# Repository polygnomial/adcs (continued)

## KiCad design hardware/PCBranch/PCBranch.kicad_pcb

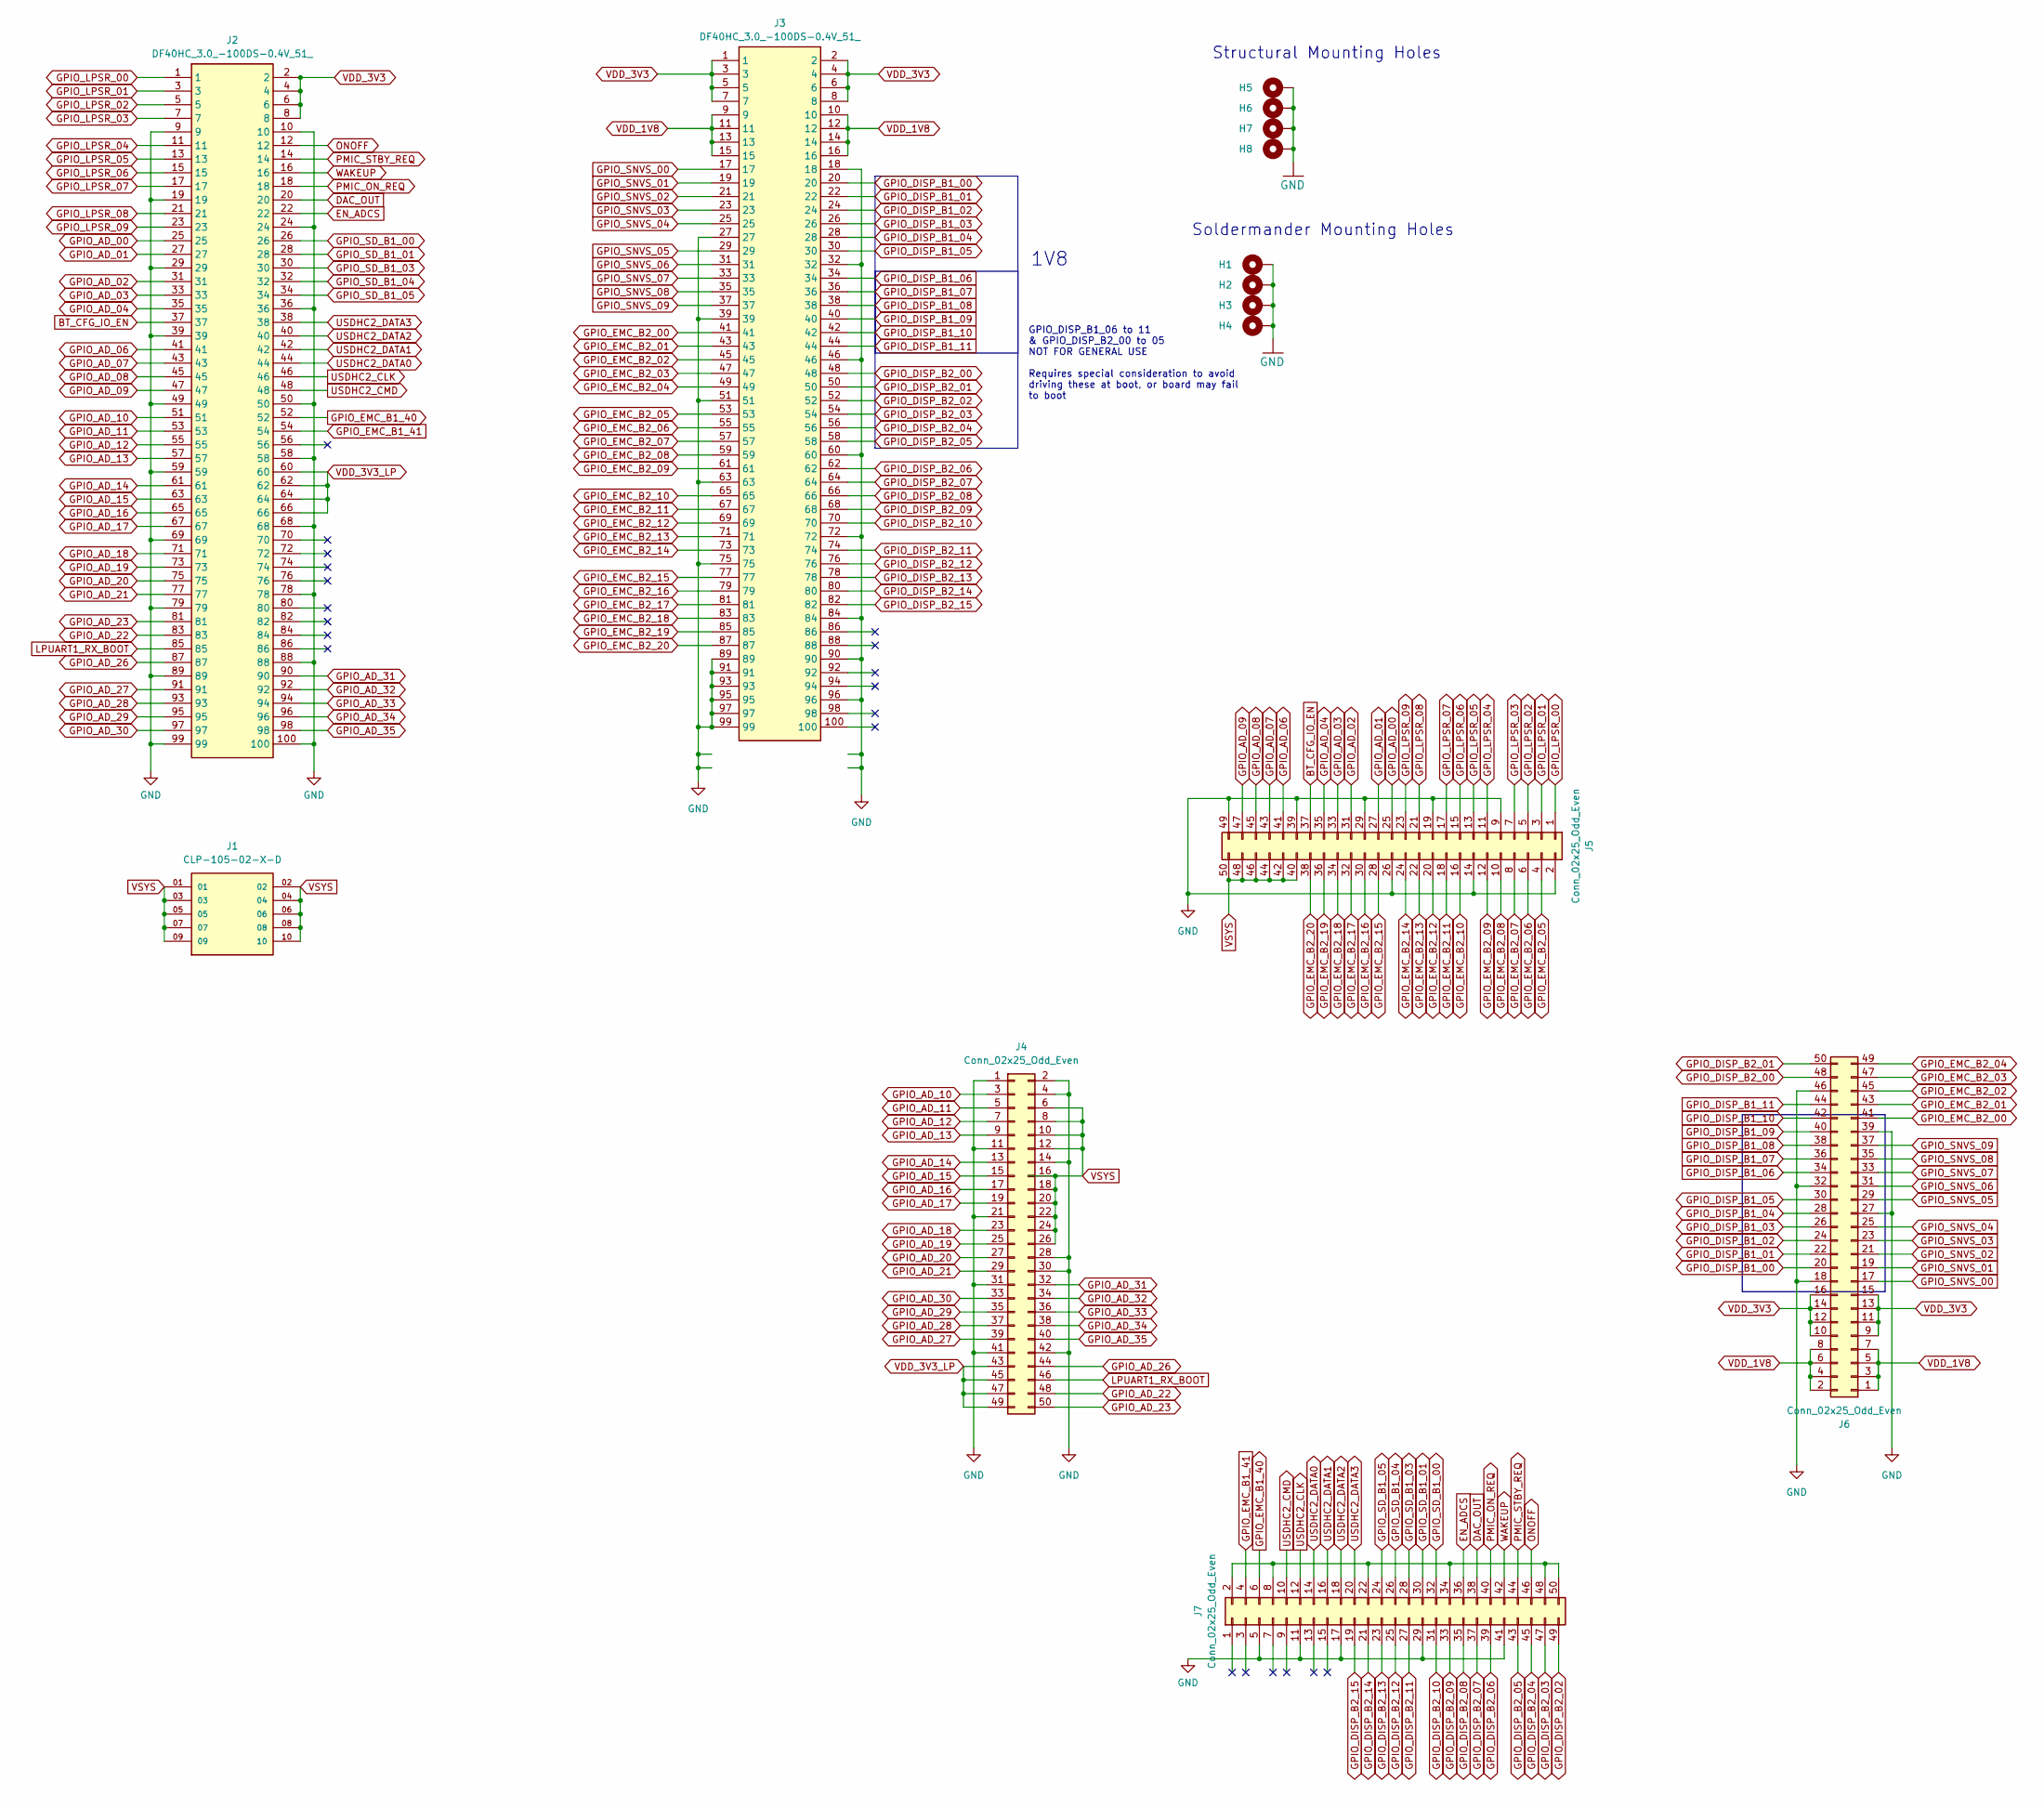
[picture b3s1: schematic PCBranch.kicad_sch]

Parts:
H1, H2, H3, H4: MountingHole_Pad; MountingHole_2.7mm_M2.5_DIN965_Pad
H5, H6, H7, H8: MountingHole_Pad; MountingHole_3.2mm_M3_DIN965_Pad
J1: CLP-105-02-X-D; SAMTEC_CLP-105-02-X-D; PARTREV V
J2, J3: DF40HC_3.0_-100DS-0.4V_51_; DF40HC30100DS04V51; Manufacturer_Part_Number DF40HC(3.0)-100DS-0.4V(51)
J4, J5, J6, J7: Conn_02x25_Odd_Even; PinHeader_2x25_P2.54mm_Vertical

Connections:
BT_CFG_IO_EN: J2.37, J5.37
DAC_OUT: J2.20, J7.38
EN_ADCS: J2.22, J7.36
GND: H1.1, H2.1, H3.1, H4.1, H5.1, H6.1, H7.1, H8.1, J2.9, J2.10, J2.19, J2.24, J2.29, J2.36, J2.39, J2.49, J2.50, J2.58, J2.59, J2.68, J2.69, J2.78, J2.79, J2.88, J2.89, J2.99, J2.100, J3.18, J3.27, J3.32, J3.39, J3.46, J3.51, J3.60, J3.63, J3.72, J3.75, J3.84, J3.89, J3.90, J3.91, J3.93, J3.95, J3.96, J3.97, J3.99, J4.1, J4.2, J4.4, J4.11, J4.14, J4.21, J4.28, J4.30, J4.31, J4.41, J4.42, J5.2, J5.9, J5.14, J5.19, J5.26, J5.29, J5.39, J5.49, J6.18, J6.27, J6.32, J6.39, J6.46, J7.5, J7.11, J7.17, J7.29, J7.41
GPIO_AD_00: J2.25, J5.25
GPIO_AD_01: J2.27, J5.27
GPIO_AD_02: J2.31, J5.31
GPIO_AD_03: J2.33, J5.33
GPIO_AD_04: J2.35, J5.35
GPIO_AD_06: J2.41, J5.41
GPIO_AD_07: J2.43, J5.43
GPIO_AD_08: J2.45, J5.45
GPIO_AD_09: J2.47, J5.47
GPIO_AD_10: J2.51, J4.3
GPIO_AD_11: J2.53, J4.5
GPIO_AD_12: J2.55, J4.7
GPIO_AD_13: J2.57, J4.9
GPIO_AD_14: J2.61, J4.13
GPIO_AD_15: J2.63, J4.15
GPIO_AD_16: J2.65, J4.17
GPIO_AD_17: J2.67, J4.19
GPIO_AD_18: J2.71, J4.23
GPIO_AD_19: J2.73, J4.25
GPIO_AD_20: J2.75, J4.27
GPIO_AD_21: J2.77, J4.29
GPIO_AD_22: J2.83, J4.48
GPIO_AD_23: J2.81, J4.50
GPIO_AD_26: J2.87, J4.44
GPIO_AD_27: J2.91, J4.39
GPIO_AD_28: J2.93, J4.37
GPIO_AD_29: J2.95, J4.35
GPIO_AD_30: J2.97, J4.33
GPIO_AD_31: J2.90, J4.32
GPIO_AD_32: J2.92, J4.34
GPIO_AD_33: J2.94, J4.36
GPIO_AD_34: J2.96, J4.38
GPIO_AD_35: J2.98, J4.40
GPIO_DISP_B1_00: J3.20, J6.20
GPIO_DISP_B1_01: J3.22, J6.22
GPIO_DISP_B1_02: J3.24, J6.24
GPIO_DISP_B1_03: J3.26, J6.26
GPIO_DISP_B1_04: J3.28, J6.28
GPIO_DISP_B1_05: J3.30, J6.30
GPIO_DISP_B1_06: J3.34, J6.34
GPIO_DISP_B1_07: J3.36, J6.36
GPIO_DISP_B1_08: J3.38, J6.38
GPIO_DISP_B1_09: J3.40, J6.40
GPIO_DISP_B1_10: J3.42, J6.42
GPIO_DISP_B1_11: J3.44, J6.44
GPIO_DISP_B2_00: J3.48, J6.48
GPIO_DISP_B2_01: J3.50, J6.50
GPIO_DISP_B2_02: J3.52, J7.49
GPIO_DISP_B2_03: J3.54, J7.47
GPIO_DISP_B2_04: J3.56, J7.45
GPIO_DISP_B2_05: J3.58, J7.43
GPIO_DISP_B2_06: J3.62, J7.39
GPIO_DISP_B2_07: J3.64, J7.37
GPIO_DISP_B2_08: J3.66, J7.35
GPIO_DISP_B2_09: J3.68, J7.33
GPIO_DISP_B2_10: J3.70, J7.31
GPIO_DISP_B2_11: J3.74, J7.27
GPIO_DISP_B2_12: J3.76, J7.25
GPIO_DISP_B2_13: J3.78, J7.23
GPIO_DISP_B2_14: J3.80, J7.21
GPIO_DISP_B2_15: J3.82, J7.19
GPIO_EMC_B1_40: J2.52, J7.6
GPIO_EMC_B1_41: J2.54, J7.4
GPIO_EMC_B2_00: J3.41, J6.41
GPIO_EMC_B2_01: J3.43, J6.43
GPIO_EMC_B2_02: J3.45, J6.45
GPIO_EMC_B2_03: J3.47, J6.47
GPIO_EMC_B2_04: J3.49, J6.49
GPIO_EMC_B2_05: J3.53, J5.4
GPIO_EMC_B2_06: J3.55, J5.6
GPIO_EMC_B2_07: J3.57, J5.8
GPIO_EMC_B2_08: J3.59, J5.10
GPIO_EMC_B2_09: J3.61, J5.12
GPIO_EMC_B2_10: J3.65, J5.16
GPIO_EMC_B2_11: J3.67, J5.18
GPIO_EMC_B2_12: J3.69, J5.20
GPIO_EMC_B2_13: J3.71, J5.22
GPIO_EMC_B2_14: J3.73, J5.24
GPIO_EMC_B2_15: J3.77, J5.28
GPIO_EMC_B2_16: J3.79, J5.30
GPIO_EMC_B2_17: J3.81, J5.32
GPIO_EMC_B2_18: J3.83, J5.34
GPIO_EMC_B2_19: J3.85, J5.36
GPIO_EMC_B2_20: J3.87, J5.38
GPIO_LPSR_00: J2.1, J5.1
GPIO_LPSR_01: J2.3, J5.3
GPIO_LPSR_02: J2.5, J5.5
GPIO_LPSR_03: J2.7, J5.7
GPIO_LPSR_04: J2.11, J5.11
GPIO_LPSR_05: J2.13, J5.13
GPIO_LPSR_06: J2.15, J5.15
GPIO_LPSR_07: J2.17, J5.17
GPIO_LPSR_08: J2.21, J5.21
GPIO_LPSR_09: J2.23, J5.23
GPIO_SD_B1_00: J2.26, J7.32
GPIO_SD_B1_01: J2.28, J7.30
GPIO_SD_B1_03: J2.30, J7.28
GPIO_SD_B1_04: J2.32, J7.26
GPIO_SD_B1_05: J2.34, J7.24
GPIO_SNVS_00: J3.17, J6.17
GPIO_SNVS_01: J3.19, J6.19
GPIO_SNVS_02: J3.21, J6.21
GPIO_SNVS_03: J3.23, J6.23
GPIO_SNVS_04: J3.25, J6.25
GPIO_SNVS_05: J3.29, J6.29
GPIO_SNVS_06: J3.31, J6.31
GPIO_SNVS_07: J3.33, J6.33
GPIO_SNVS_08: J3.35, J6.35
GPIO_SNVS_09: J3.37, J6.37
LPUART1_RX_BOOT: J2.85, J4.46
unnamed: J7.2, J7.8, J7.22, J7.34, J7.48, J7.50
ONOFF: J2.12, J7.46
PMIC_ON_REQ: J2.18, J7.40
PMIC_STBY_REQ: J2.14, J7.44
USDHC2_CLK: J2.46, J7.12
USDHC2_CMD: J2.48, J7.10
USDHC2_DATA0: J2.44, J7.14
USDHC2_DATA1: J2.42, J7.16
USDHC2_DATA2: J2.40, J7.18
USDHC2_DATA3: J2.38, J7.20
VDD_1V8: J3.9, J3.10, J3.11, J3.12, J3.13, J3.14, J3.15, J3.16, J6.1, J6.2, J6.3, J6.4, J6.5, J6.6, J6.7, J6.8
VDD_3V3: J2.2, J2.4, J2.6, J2.8, J3.1, J3.2, J3.3, J3.4, J3.5, J3.6, J3.7, J3.8, J6.9, J6.10, J6.11, J6.12, J6.13, J6.14, J6.15, J6.16
VDD_3V3_LP: J2.60, J2.62, J2.64, J2.66, J4.43, J4.45, J4.47, J4.49
VSYS: J1.01, J1.02, J1.03, J1.04, J1.05, J1.06, J1.07, J1.08, J1.09, J1.10, J4.6, J4.8, J4.10, J4.12, J4.16, J4.18, J4.20, J4.22, J4.24, J4.26, J5.40, J5.42, J5.44, J5.46, J5.48, J5.50
WAKEUP: J2.16, J7.42

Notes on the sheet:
1V8
Soldermander Mounting Holes
Structural Mounting Holes
GPIO_DISP_B1_06 to 11 & GPIO_DISP_B2_00 to 05 NOT FOR GENERAL USE Requires special consideration to avoid driving these at boot, or board may fail to boot

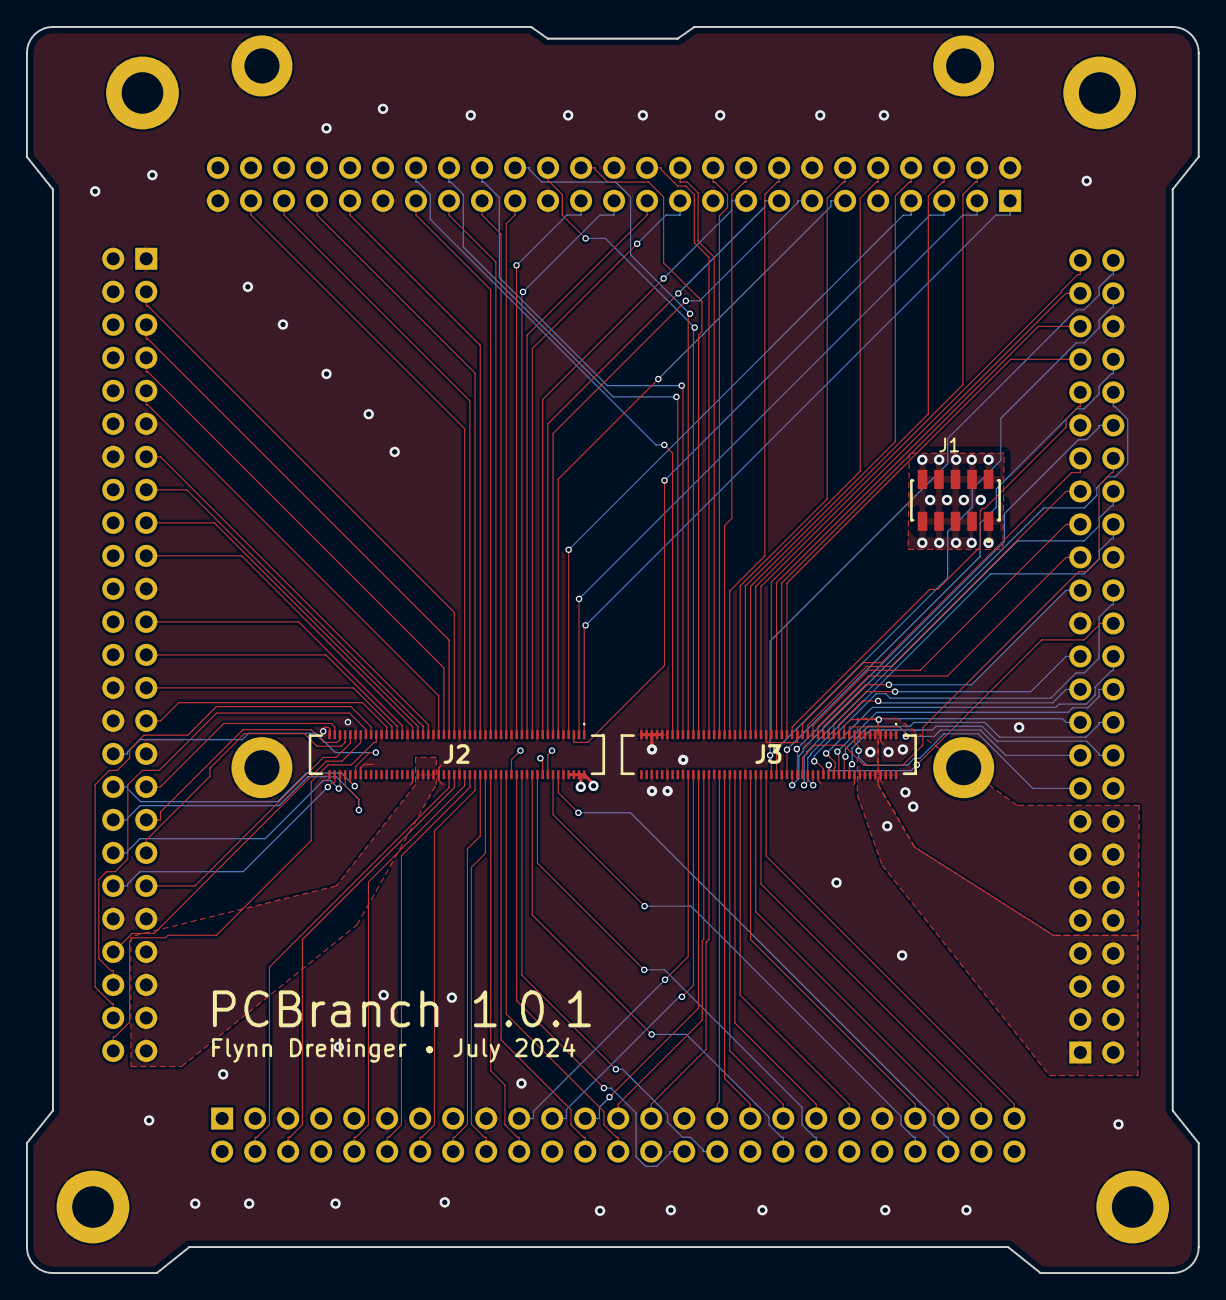
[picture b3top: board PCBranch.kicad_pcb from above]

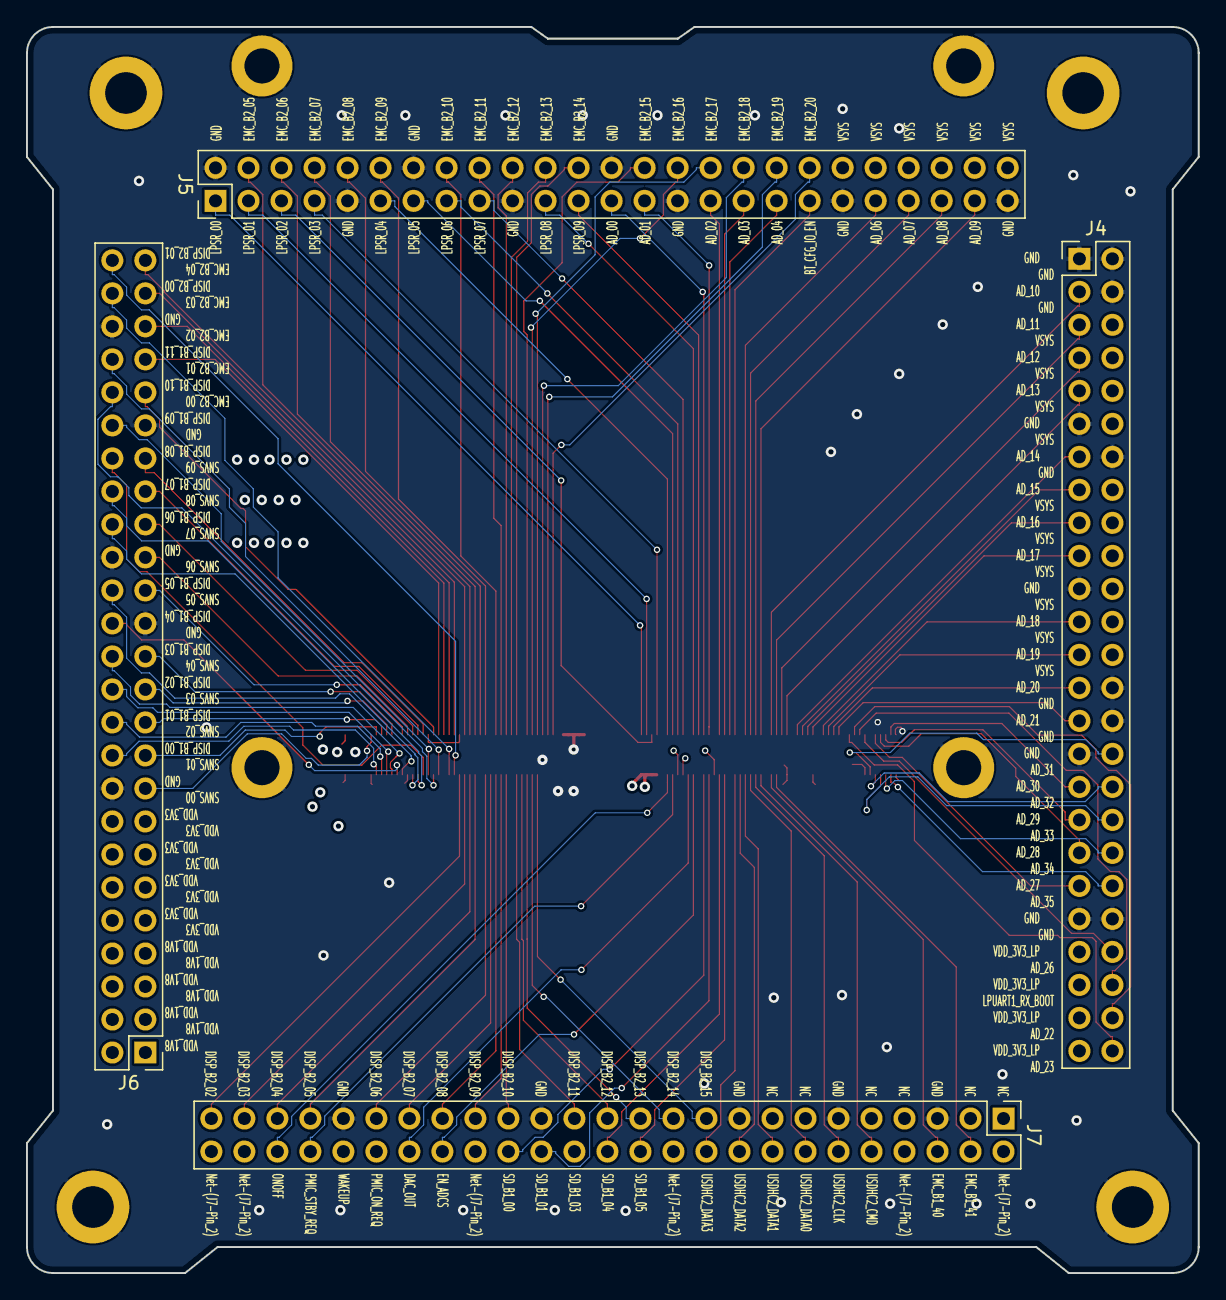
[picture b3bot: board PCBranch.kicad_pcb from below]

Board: 4 copper layers, 90.2 x 95.9 mm, 15 parts (4 on the bottom side), 129 nets.

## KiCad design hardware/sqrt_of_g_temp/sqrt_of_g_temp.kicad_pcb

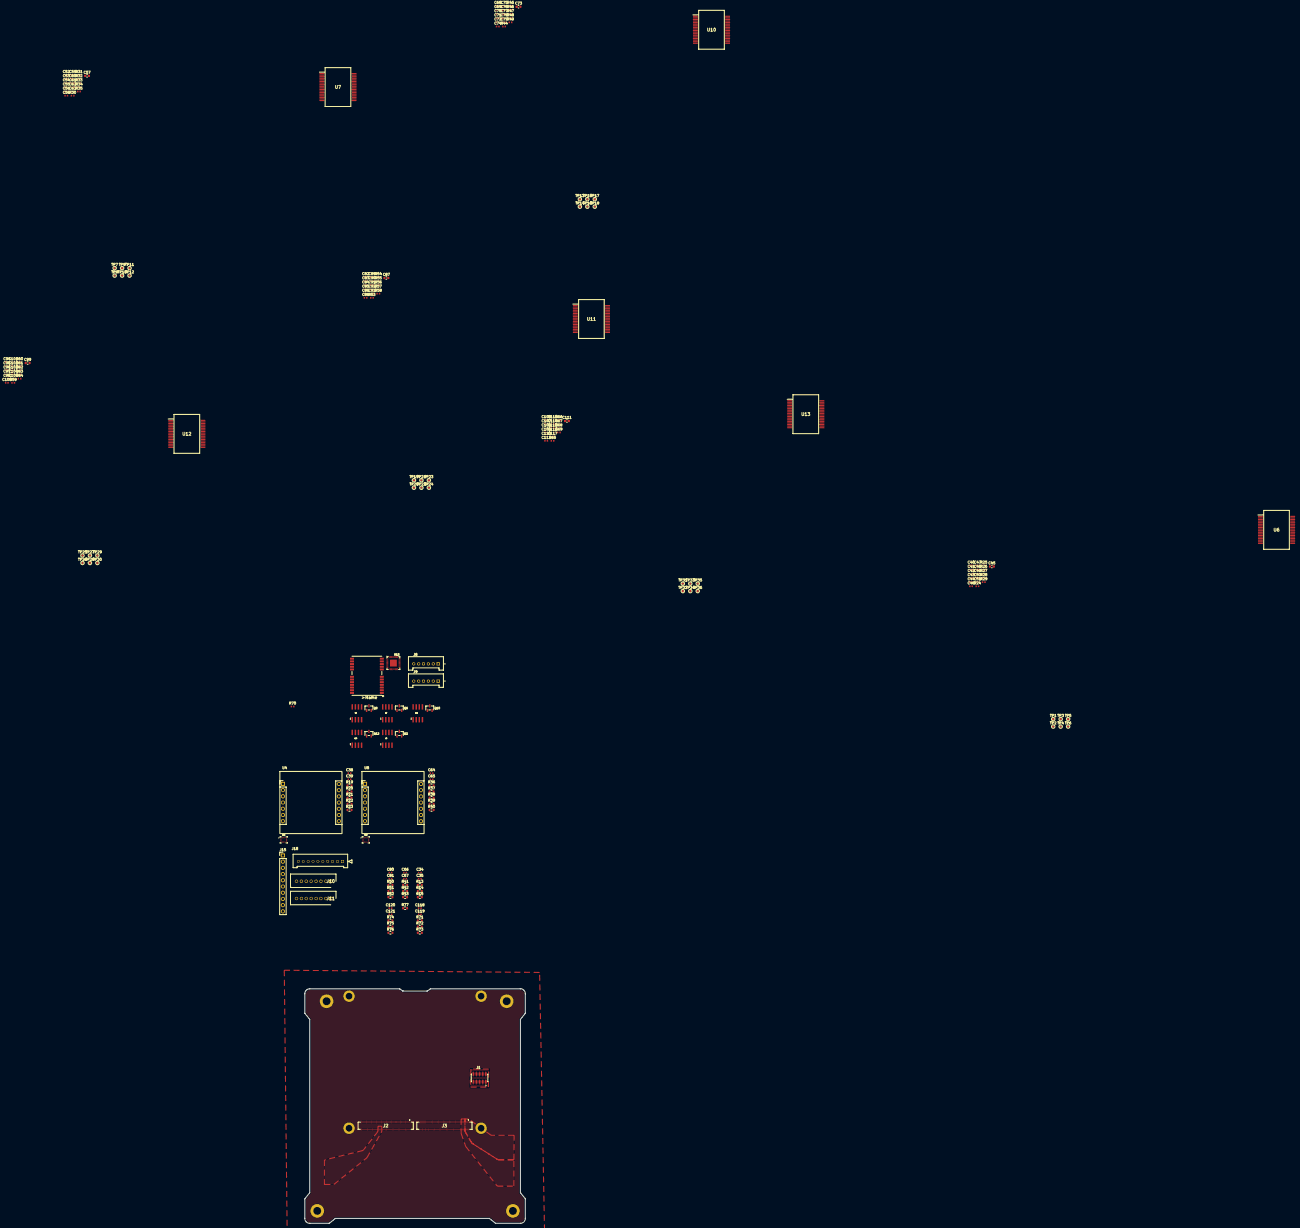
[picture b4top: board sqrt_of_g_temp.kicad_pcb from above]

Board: 4 copper layers, 90.2 x 95.9 mm, 223 parts (0 on the bottom side), 128 nets, no tracks yet.

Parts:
C34, C66, C80, C118, C120: 10nF; Perfect_0402
C35, C67, C81, C119, C121: 4.7uF; Perfect_0402
C38, C39, C48, C50, C51, C60, C62, C63, C64, C65, C76, C78, C79, C90, C92, C93, C102, C104, C105, C114, C116, C117: 0.1uF; Perfect_0402
C40, C41, C42, C44, C46, C47, C49, C52, C53, C54, C56, C58, C59, C61, C68, C69, C70, C72, C74, C75, C77, C82, C83, C84, C86, C88, C89, C91, C94, C95, C96, C98, C100, C101, C103, C106, C107, C108, C110, C112, C113, C115: 100nF; Perfect_0402
C43, C55, C71, C85, C97, C109: 1uF; Perfect_0402
C45, C57, C73, C87, C99, C111: 47uF; C_0603_1608Metric
H1, H2, H3, H4: MountingHole_Pad; MountingHole_2.7mm_M2.5_DIN965_Pad
H5, H6, H7, H8: MountingHole_Pad; MountingHole_3.2mm_M3_DIN965_Pad
J1: CLP-105-02-X-D; SAMTEC_CLP-105-02-X-D
J2, J3: DF40HC_3.0_-100DS-0.4V_51_; DF40HC30100DS04V51
J8, J9: 353620650; MOLEX_35362-0650
J10, J11: 353620850; SHDR8W50P0X200_1X8_1830X550X850P
J15: Conn_01x10; PinHeader_1x10_P2.54mm_Vertical
J18: Thruster Connector; CON_353621050
Q2, Q6, Q8, Q10, Q12: IRLML2803; SOT-23
Q3, Q7, Q9, Q11, Q13: NDS8434
R13, R41, R50, R71, R74, R77: 10K; R_0603_1608Metric
R14, R42, R51, R72, R75: 4.7K; R_0603_1608Metric
R15, R43, R52, R73, R76: 3.3k; R_0603_1608Metric
R19, R20, R21, R22, R23, R36, R37, R38, R39, R40: 10k; R_0603_1608Metric
R24, R27, R28, R29, R30, R33, R34, R35, R44, R47, R48, R49, R53, R56, R57, R58, R59, R62, R63, R64, R65, R68, R69, R70: 10k; Perfect_0402
R25, R31, R45, R54, R60, R66: 36k; Perfect_0402
R26, R32, R46, R55, R61, R67: 1; Perfect_0402
TP1, TP2, TP3, TP4, TP5, TP6, TP7, TP8, TP9, TP10, TP11, TP12, TP13, TP14, TP15, TP16, TP17, TP18, TP19, TP20, TP21, TP22, TP23, TP24, TP25, TP26, TP27, TP28, TP29, TP30, TP31, TP32, TP33, TP34, TP35, TP36: TestPoint; TestPoint_Pad_D1.0mm
U4, U8: RM3100 Dev Board; RM3100
U5, U9: BMI270; XDCR_BMI270
U6, U7, U10, U11, U12, U13: DRV8332DKDR; SOP65P1420X360-36N
U14: Orion B16; S1216_24PIN_PACKAGE
U15: EP2W+; QFN32-5X5MM

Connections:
+3V3: J15.1, Q3.1 (Source), Q3.2 (Source), Q3.3 (Source), Q7.1 (Source), Q7.2 (Source), Q7.3 (Source), Q9.1 (Source), Q9.2 (Source), Q9.3 (Source), Q11.1 (Source), Q11.2 (Source), Q11.3 (Source), Q13.1 (Source), Q13.2 (Source), Q13.3 (Source), R15.1, R43.1, R52.1, R73.1, R76.1
+12V: C43.2, C45.2, C46.1, C47.1, C48.1, C49.1, C50.1, C51.1, C55.2, C57.2, C58.1, C59.1, C60.1, C61.1, C62.1, C63.1, C71.2, C73.2, C74.1, C75.1, C76.1, C77.1, C78.1, C79.1, C85.2, C87.2, C88.1, C89.1, C90.1, C91.1, C92.1, C93.1, C97.2, C99.2, C100.1, C101.1, C102.1, C103.1, C104.1, C105.1, C109.2, C111.2, C112.1, C113.1, C114.1, C115.1, C116.1, C117.1, U6.1 (GVDD_B), U6.18 (GVDD_C), U6.19 (GVDD_C), U6.21 (PVDD_C), U6.29 (PVDD_B), U6.34 (PVDD_A), U6.36 (GVDD_A), U7.1 (GVDD_B), U7.18 (GVDD_C), U7.19 (GVDD_C), U7.21 (PVDD_C), U7.29 (PVDD_B), U7.34 (PVDD_A), U7.36 (GVDD_A), U10.1 (GVDD_B), U10.18 (GVDD_C), U10.19 (GVDD_C), U10.21 (PVDD_C), U10.29 (PVDD_B), U10.34 (PVDD_A), U10.36 (GVDD_A), U11.1 (GVDD_B), U11.18 (GVDD_C), U11.19 (GVDD_C), U11.21 (PVDD_C), U11.29 (PVDD_B), U11.34 (PVDD_A), U11.36 (GVDD_A), U12.1 (GVDD_B), U12.18 (GVDD_C), U12.19 (GVDD_C), U12.21 (PVDD_C), U12.29 (PVDD_B), U12.34 (PVDD_A), U12.36 (GVDD_A), U13.1 (GVDD_B), U13.18 (GVDD_C), U13.19 (GVDD_C), U13.21 (PVDD_C), U13.29 (PVDD_B), U13.34 (PVDD_A), U13.36 (GVDD_A)
/3V3_PD1: C80.1, C81.1, J9.1, J11.1, J11.5, Q9.5 (Drain), Q9.6 (Drain), Q9.7 (Drain), Q9.8 (Drain)
/3V3_PD2: C66.1, C67.1, J8.1, J10.1, J10.5, Q7.5 (Drain), Q7.6 (Drain), Q7.7 (Drain), Q7.8 (Drain)
/GPS/3V3_GPS: C118.1, C119.1, Q11.5 (Drain), Q11.6 (Drain), Q11.7 (Drain), Q11.8 (Drain), R77.2, U14.22 (V_BCKP), U14.23 (VCC)
/GPS/EN_GPS: R71.1, R72.1
/GPS/RF_IN: U14.11 (RF_IN), U15.4 (SUM_PORT)
/IMU1_and_MAG1/3V3_SENSORS: C38.1, C39.1, C120.1, C121.1, Q13.5 (Drain), Q13.6 (Drain), Q13.7 (Drain), Q13.8 (Drain), R21.2, R22.1, R23.1, U4.12 (DVDD), U4.13 (AVDD), U5.5 (VDDIO), U5.8 (VDD), U5.10 (OSCB)
/IMU1_and_MAG1/EN_SENSORS: R74.1, R75.1
/IMU2_and_MAG2/3V3_SENSORS: C34.1, C35.1, C64.1, C65.1, Q3.5 (Drain), Q3.6 (Drain), Q3.7 (Drain), Q3.8 (Drain), R38.2, R39.1, R40.1, U8.12 (DVDD), U8.13 (AVDD), U9.5 (VDDIO), U9.8 (VDD), U9.10 (OSCB)
/IMU2_and_MAG2/EN_SENSORS: R13.1, R14.1
/Magnetorquer Controller 1/AGND: C106.1, R66.1, R67.2, U13.9 (AGND), U13.12 (M2)
/Magnetorquer Controller 1/M1: R65.2, U13.13 (M1)
/Magnetorquer Controller 1/OUT_A: C107.1, U13.33 (OUT_A)
/Magnetorquer Controller 1/OUT_B: C108.1, U13.30 (OUT_B)
/Magnetorquer Controller 1/OUT_C: C110.1, U13.22 (OUT_C)
/Magnetorquer Controller 2/AGND: C40.1, R25.1, R26.2, U6.9 (AGND), U6.12 (M2)
/Magnetorquer Controller 2/M1: R24.2, U6.13 (M1)
/Magnetorquer Controller 2/OUT_A: C41.1, U6.33 (OUT_A)
/Magnetorquer Controller 2/OUT_B: C42.1, U6.30 (OUT_B)
/Magnetorquer Controller 2/OUT_C: C44.1, U6.22 (OUT_C)
/Motor Controller 1/AGND: C82.1, R54.1, R55.2, U11.9 (AGND), U11.12 (M2)
/Motor Controller 1/M1: R53.2, U11.13 (M1)
/Motor Controller 1/OUT_A: C83.1, U11.33 (OUT_A)
/Motor Controller 1/OUT_B: C84.1, U11.30 (OUT_B)
/Motor Controller 1/OUT_C: C86.1, U11.22 (OUT_C)
/Motor Controller 2/AGND: C52.1, R31.1, R32.2, U7.9 (AGND), U7.12 (M2)
/Motor Controller 2/M1: R30.2, U7.13 (M1)
/Motor Controller 2/OUT_A: C53.1, U7.33 (OUT_A)
/Motor Controller 2/OUT_B: C54.1, U7.30 (OUT_B)
/Motor Controller 2/OUT_C: C56.1, U7.22 (OUT_C)
/Motor Controller 3/AGND: C94.1, R60.1, R61.2, U12.9 (AGND), U12.12 (M2)
/Motor Controller 3/M1: R59.2, U12.13 (M1)
/Motor Controller 3/OUT_A: C95.1, U12.33 (OUT_A)
/Motor Controller 3/OUT_B: C96.1, U12.30 (OUT_B)
/Motor Controller 3/OUT_C: C98.1, U12.22 (OUT_C)
/Motor Controller 4/AGND: C68.1, R45.1, R46.2, U10.9 (AGND), U10.12 (M2)
/Motor Controller 4/M1: R44.2, U10.13 (M1)
/Motor Controller 4/OUT_A: C69.1, U10.33 (OUT_A)
/Motor Controller 4/OUT_B: C70.1, U10.30 (OUT_B)
/Motor Controller 4/OUT_C: C72.1, U10.22 (OUT_C)
/Photodiode Enable 1/EN: R50.1, R51.1
/Photodiode Enable 2/EN: R41.1, R42.1
/SCL2: R22.2, U4.1 (SCK/SCL), U5.13 (SCX)
/SCL4: R39.2, U8.1 (SCK/SCL), U9.13 (SCX)
/SDA2: R23.2, U4.3 (SI/SDA), U5.14 (SDX)
/SDA4: R40.2, U8.3 (SI/SDA), U9.14 (SDX)
GND: C38.2, C39.2, C46.2, C47.2, C48.2, C49.2, C50.2, C51.2, C58.2, C59.2, C60.2, C61.2, C62.2, C63.2, C64.2, C65.2, C74.2, C75.2, C76.2, C77.2, C78.2, C79.2, C88.2, C89.2, C90.2, C91.2, C92.2, C93.2, C100.2, C101.2, C102.2, C103.2, C104.2, C105.2, C112.2, C113.2, C114.2, C115.2, C116.2, C117.2, H1.1, H2.1, H3.1, H4.1, H5.1, H6.1, H7.1, H8.1, J2.9, J2.10, J2.19, J2.24, J2.29, J2.36, J2.39, J2.49, J2.50, J2.58, J2.59, J2.68, J2.69, J2.78, J2.79, J2.88, J2.89, J2.99, J2.100, J3.18, J3.27, J3.32, J3.39, J3.46, J3.51, J3.60, J3.63, J3.72, J3.75, J3.84, J3.89, J3.90, J3.91, J3.93, J3.95, J3.96, J3.97, J3.99, J8.2, J9.2, J10.2, J10.6, J11.2, J11.6, J15.10, J18.1, J18.10, Q2.2 (S), Q6.2 (S), Q8.2 (S), Q10.2 (S), Q12.2 (S), R13.2, R19.1, R20.1, R24.1, R26.1, R27.1, R28.1, R29.1, R30.1, R32.1, R33.1, R34.1, R35.1, R36.1, R37.1, R41.2, R44.1, R46.1, R47.1, R48.1, R49.1, R50.2, R53.1, R55.1, R56.1, R57.1, R58.1, R59.1, R61.1, R62.1, R63.1, R64.1, R65.1, R67.1, R68.1, R69.1, R70.1, R71.2, R74.2, TP2.1, TP4.1, TP6.1, TP8.1, TP10.1, TP12.1, TP14.1, TP16.1, TP18.1, TP20.1, TP22.1, TP24.1, TP26.1, TP28.1, TP30.1, TP32.1, TP34.1, TP36.1, U4.7 (AVSS), U4.14 (DVSS), U5.1 (SDO), U5.6 (GNDIO), U5.7 (GND), U6.8 (GND), U6.24 (GND), U6.25 (GND), U7.8 (GND), U7.24 (GND), U7.25 (GND), U8.7 (AVSS), U8.14 (DVSS), U9.1 (SDO), U9.6 (GNDIO), U9.7 (GND), U10.8 (GND), U10.24 (GND), U10.25 (GND), U11.8 (GND), U11.24 (GND), U11.25 (GND), U12.8 (GND), U12.24 (GND), U12.25 (GND), U13.8 (GND), U13.24 (GND), U13.25 (GND), U14.10 (GND@10), U14.12 (GND@12), U14.13 (GND@13), U14.24 (GND@24), U15.1 (GND), U15.2 (GND), U15.3 (GND), U15.5 (GND), U15.6 (GND), U15.7 (GND), U15.8 (GND), U15.9 (GND), U15.10 (GND), U15.11 (GND), U15.12 (GND), U15.13 (GND), U15.14 (GND), U15.16 (GND), U15.17 (GND), U15.18 (GND), U15.19 (GND), U15.20 (GND), U15.21 (GND), U15.22 (GND), U15.23 (GND), U15.24 (GND), U15.25 (GND), U15.27 (GND), U15.28 (GND), U15.29 (GND), U15.30 (GND), U15.31 (GND), U15.32 (GND), U15.EP (GND)
unnamed: C34.2, C35.2
unnamed: C66.2, C67.2
unnamed: C80.2, C81.2
unnamed: C118.2, C119.2
unnamed: C120.2, C121.2
unnamed: Q2.3 (D), Q3.4 (Gate), R15.2
unnamed: Q2.1 (G), R14.2
unnamed: Q6.3 (D), Q7.4 (Gate), R43.2
unnamed: Q6.1 (G), R42.2
unnamed: Q8.3 (D), Q9.4 (Gate), R52.2
unnamed: Q8.1 (G), R51.2
unnamed: Q10.3 (D), Q11.4 (Gate), R73.2
unnamed: Q10.1 (G), R72.2
unnamed: Q12.3 (D), Q13.4 (Gate), R76.2
unnamed: Q12.1 (G), R75.2
unnamed: R21.1, U4.10 (I2CEN)
unnamed: R19.2, U4.2 (SO/ADDR1)
unnamed: R20.2, U4.4 (SSN/ADDR0)
unnamed: C41.2, U6.35 (BST_A)
unnamed: C42.2, U6.28 (BST_B)
unnamed: C44.2, U6.20 (BST_C)
unnamed: R29.2, TP5.1, U6.32 (GND_A)
unnamed: R28.2, TP3.1, U6.31 (GND_B)
unnamed: R27.2, TP1.1, U6.23 (GND_C)
unnamed: R25.2, U6.7 (OC_ADJ)
unnamed: C43.1, C45.1, U6.17 (VDD)
unnamed: C40.2, U6.10 (VREG)
unnamed: C53.2, U7.35 (BST_A)
unnamed: C54.2, U7.28 (BST_B)
unnamed: C56.2, U7.20 (BST_C)
unnamed: R35.2, TP11.1, U7.32 (GND_A)
unnamed: R34.2, TP9.1, U7.31 (GND_B)
unnamed: R33.2, TP7.1, U7.23 (GND_C)
unnamed: R31.2, U7.7 (OC_ADJ)
unnamed: C55.1, C57.1, U7.17 (VDD)
unnamed: C52.2, U7.10 (VREG)
unnamed: R38.1, U8.10 (I2CEN)
unnamed: R36.2, U8.2 (SO/ADDR1)
unnamed: R37.2, U8.4 (SSN/ADDR0)
unnamed: C69.2, U10.35 (BST_A)
unnamed: C70.2, U10.28 (BST_B)
unnamed: C72.2, U10.20 (BST_C)
unnamed: R49.2, TP17.1, U10.32 (GND_A)
unnamed: R48.2, TP15.1, U10.31 (GND_B)
unnamed: R47.2, TP13.1, U10.23 (GND_C)
unnamed: R45.2, U10.7 (OC_ADJ)
unnamed: C71.1, C73.1, U10.17 (VDD)
unnamed: C68.2, U10.10 (VREG)
unnamed: C83.2, U11.35 (BST_A)
unnamed: C84.2, U11.28 (BST_B)
unnamed: C86.2, U11.20 (BST_C)
unnamed: R58.2, TP23.1, U11.32 (GND_A)
unnamed: R57.2, TP21.1, U11.31 (GND_B)
unnamed: R56.2, TP19.1, U11.23 (GND_C)
unnamed: R54.2, U11.7 (OC_ADJ)
unnamed: C85.1, C87.1, U11.17 (VDD)
unnamed: C82.2, U11.10 (VREG)
unnamed: C95.2, U12.35 (BST_A)
unnamed: C96.2, U12.28 (BST_B)
unnamed: C98.2, U12.20 (BST_C)
unnamed: R64.2, TP29.1, U12.32 (GND_A)
unnamed: R63.2, TP27.1, U12.31 (GND_B)
unnamed: R62.2, TP25.1, U12.23 (GND_C)
unnamed: R60.2, U12.7 (OC_ADJ)
unnamed: C97.1, C99.1, U12.17 (VDD)
unnamed: C94.2, U12.10 (VREG)
unnamed: C107.2, U13.35 (BST_A)
unnamed: C108.2, U13.28 (BST_B)
unnamed: C110.2, U13.20 (BST_C)
unnamed: R70.2, TP35.1, U13.32 (GND_A)
unnamed: R69.2, TP33.1, U13.31 (GND_B)
unnamed: R68.2, TP31.1, U13.23 (GND_C)
unnamed: R66.2, U13.7 (OC_ADJ)
unnamed: C109.1, C111.1, U13.17 (VDD)
unnamed: C106.2, U13.10 (VREG)
unnamed: R77.1, U14.8 (RSTN)
VDD_1V8: J3.9, J3.10, J3.11, J3.12, J3.13, J3.14, J3.15, J3.16
VDD_3V3: J2.2, J2.4, J2.6, J2.8, J3.1, J3.2, J3.3, J3.4, J3.5, J3.6, J3.7, J3.8
VDD_3V3_LP: J2.60, J2.62, J2.64, J2.66
VSYS: J1.01, J1.02, J1.03, J1.04, J1.05, J1.06, J1.07, J1.08, J1.09, J1.10

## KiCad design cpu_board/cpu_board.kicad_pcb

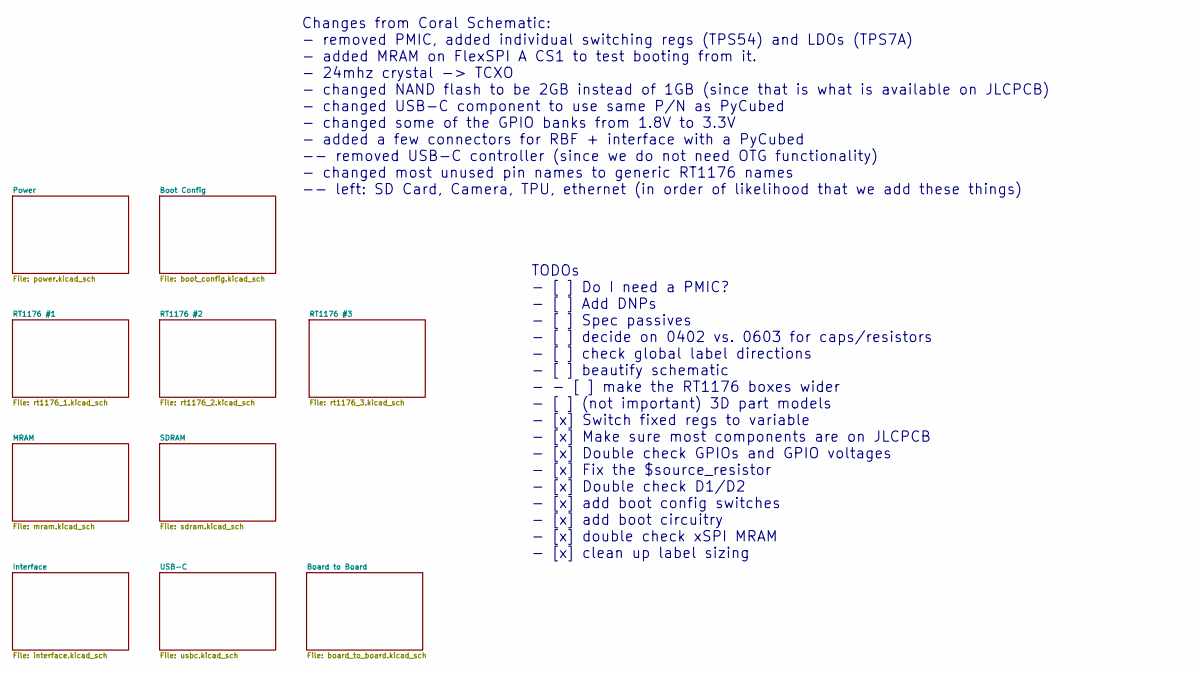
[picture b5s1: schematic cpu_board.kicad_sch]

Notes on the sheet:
Changes from Coral Schematic: - removed PMIC, added individual switching regs (TPS54) and LDOs (TPS7A) - added MRAM on FlexSPI A CS1 to test booting from it. - 24mhz crystal -> TCXO - changed NAND flash to be 2GB instead of 1GB (since that is what is available on JLCPCB) - changed USB-C component t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
TODOs - [ ] Do I need a PMIC? - [ ] Add DNPs - [ ] Spec passives - [ ] decide on 0402 vs. 0603 for caps/resistors - [ ] check global label directions - [ ] beautify schematic - - [ ] make the RT1176 boxes wider - [ ] (not important) 3D part models - [x] Switch fixed regs to variable - [x] Make sure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
